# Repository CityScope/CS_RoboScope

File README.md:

# RoboScope

RoboScop project is an motorize platform and three-dimensional interactive simulation platform for the understanding of urban environments. The platform is made of an array of 3D Pixels that can be configured in varying heights and color to represent different urban conditions. In addition, each pixel

## Circuits

Circuits designs in Eagle

## Code

Source code to run the each one of the different project components, server, client, control and interface.

## Docs

Folder includes designs files, drawings, technical data-sheets, and assembly instructions.

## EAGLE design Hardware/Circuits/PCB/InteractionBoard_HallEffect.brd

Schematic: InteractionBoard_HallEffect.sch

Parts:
C1, C2, C3, C4, C5, C6, C7, C8, C9, C12, C13, C14, C15, C16, C17, C18, C19: 0.1uF; 0603-CAP
J3: F-2X10-DIL-2MM; DIL-2MM-2X10
JP1: JUMPER-SMT_3_1-NC_TRACE_NO-SILK; SMT-JUMPER_3_1-NC_TRACE_NO-SILK
JP6, JP7, JP8, JP9, JP10, JP11: JUMPER-SMT_2_NC_TRACE_NO-SILK; SMT-JUMPER_2_NC_TRACE_NO-SILK
M_01, M_02, M_03, M_04, M_05, M_06, M_07, M_08: CONN_06SMD-1MM; 1X06-1MM
POWER_3.3: LEDFAB1206; LED1206FAB
R9, R10, R11, R12, R13, R14, R16, R17, R18, R19, R20, R21, R23, R24, R25, R26: 10K; 0603-RES
R27, R28: 500; 0603-RES
RN1, RN2, RN3: 4R-NEXB38V; EXB38V
S1: JS207011SCQNR; SW_JS207011SCQNR
S2: MOMENTARY-SWITCH-SPST-2-SMD-5.2MM; TACTILE_SWITCH_SMD_5.2MM
STATUS: LEDFAB1206; LED1206FAB
SW1: 219-10; CTS-219-10
SX1509_2, SX1509_3: SX1509; QFN-28
U1, U3, U4, U5, U6, U7, U8, U9: DRV5032FADBZRDBZ0003A_L; DBZ0003A_L
U2: SX1509; QFN-28

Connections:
0_SX1: M_04.6, SX1509_2.27 (I/O[0])
0_SX2: M_08.6, U2.27 (I/O[0])
0_SX3: SX1509_3.27 (I/O[0])
1_SX1: M_04.5, SX1509_2.28 (I/O[1])
1_SX2: M_08.5, U2.28 (I/O[1])
1_SX3: J3.16, SX1509_3.28 (I/O[1])
2_SX1: M_02.6, SX1509_2.1 (I/O[2])
2_SX2: M_06.6, U2.1 (I/O[2])
2_SX3: SX1509_3.1 (I/O[2])
3.3V: C1.1, C2.1, C3.1, C4.1, C5.1, C6.1, C7.1, C8.1, C9.1, C12.1, C13.1, C14.1, C15.1, C16.1, C17.1, C18.1, C19.1, J3.19, R9.2, R10.2, R11.2, R12.2, R13.2, R14.2, R16.2, R17.2, R18.2, R19.2, R20.2, R21.2, R23.2, R24.2, R25.2, R26.2, R27.2, RN1.5 (2), RN1.6 (2), RN1.7 (2), RN1.8 (2), RN2.7 (2), RN2.8 (2), RN3.5 (2), RN3.6 (2), RN3.7 (2), RN3.8 (2), S2.1, S2.2, SX1509_2.4 (VCC1), SX1509_2.12 (VDDM), SX1509_2.18 (VCC2), SX1509_3.4 (VCC1), SX1509_3.12 (VDDM), SX1509_3.18 (VCC2), U1.1 (VCC), U2.4 (VCC1), U2.12 (VDDM), U2.18 (VCC2), U3.1 (VCC), U4.1 (VCC), U5.1 (VCC), U6.1 (VCC), U7.1 (VCC), U8.1 (VCC), U9.1 (VCC)
3_SX1: M_02.5, SX1509_2.2 (I/O[3])
3_SX2: M_06.5, U2.2 (I/O[3])
3_SX3: J3.12, SX1509_3.2 (I/O[3])
4_SX1: M_02.4, SX1509_2.5 (I/O[4])
4_SX2: M_06.4, U2.5 (I/O[4])
4_SX3: JP1.1, SX1509_3.5 (I/O[4])
5_SX1: M_04.4, SX1509_2.6 (I/O[5])
5_SX2: M_08.4, U2.6 (I/O[5])
5_SX3: R28.2, SX1509_3.6 (I/O[5])
6_SX1: SX1509_2.7 (I/O[6]), U3.2 (OUT)
6_SX2: U2.7 (I/O[6]), U7.2 (OUT)
6_SX3: RN1.1, SW1.20, SX1509_3.7 (I/O[6])
7_SX1: SX1509_2.8 (I/O[7]), U5.2 (OUT)
7_SX2: U2.8 (I/O[7]), U9.2 (OUT)
7_SX3: RN1.2 (1), SW1.19, SX1509_3.8 (I/O[7])
8_SX1: SX1509_2.13 (I/O[8]), U1.2 (OUT)
8_SX2: U2.13 (I/O[8]), U6.2 (OUT)
8_SX3: RN1.3 (1), SW1.18, SX1509_3.13 (I/O[8])
9_SX1: SX1509_2.14 (I/O[9]), U4.2 (OUT)
9_SX2: U2.14 (I/O[9]), U8.2 (OUT)
9_SX3: RN1.4 (1), SW1.17, SX1509_3.14 (I/O[9])
10_SX1: M_01.6, SX1509_2.15 (I/O[10])
10_SX2: M_05.6, U2.15 (I/O[10])
10_SX3: RN3.1, SW1.16, SX1509_3.15 (I/O[10])
11_SX1: M_01.5, SX1509_2.16 (I/O[11])
11_SX2: M_05.5, U2.16 (I/O[11])
11_SX3: RN3.2 (1), SW1.15, SX1509_3.16 (I/O[11])
12_SX1: M_01.4, SX1509_2.19 (I/O[12])
12_SX2: M_05.4, U2.19 (I/O[12])
12_SX3: RN3.3 (1), SW1.14, SX1509_3.19 (I/O[12])
13_SX1: M_03.6, SX1509_2.20 (I/O[13])
13_SX2: M_07.6, U2.20 (I/O[13])
13_SX3: RN3.4 (1), SW1.13, SX1509_3.20 (I/O[13])
14_SX1: M_03.5, SX1509_2.21 (I/O[14])
14_SX2: M_07.5, U2.21 (I/O[14])
14_SX3: RN2.1, SW1.12, SX1509_3.21 (I/O[14])
15_SX1: M_03.4, SX1509_2.22 (I/O[15])
15_SX2: M_07.4, U2.22 (I/O[15])
15_SX3: RN2.2 (1), SW1.11, SX1509_3.22 (I/O[15])
!RESET_SX1: R9.1, SX1509_2.23 (!RESET)
!RESET_SX2: R16.1, U2.23 (!RESET)
!RESET_SX3: R14.1, SX1509_3.23 (!RESET)
ADDR0_SX1: JP8.1, SX1509_2.26 (ADDR0)
ADDR0_SX2: JP7.1, U2.26 (ADDR0)
ADDR0_SX3: JP11.1, SX1509_3.26 (ADDR0)
ADDR1_SX1: JP9.1, SX1509_2.10 (ADDR1)
ADDR1_SX2: JP6.1, U2.10 (ADDR1)
ADDR1_SX3: JP10.1, SX1509_3.10 (ADDR1)
GND_MCU: C1.2, C2.2, C3.2, C4.2, C5.2, C6.2, C7.2, C8.2, C9.2, C12.2, C13.2, C14.2, C15.2, C16.2, C17.2, C18.2, C19.2, J3.18, J3.20, JP7.2, JP9.2, M_01.1, M_02.1, M_03.1, M_04.1, M_05.1, M_06.1, M_07.1, M_08.1, POWER_3.3.2 (C), RN2.3 (1), STATUS.2 (C), SW1.1, SW1.2, SW1.3, SW1.4, SW1.5, SW1.6, SW1.7, SW1.8, SW1.9, SW1.10, SX1509_2.3 (GND), SX1509_2.17 (GND), SX1509_2.29 (GND), SX1509_3.3 (GND), SX1509_3.17 (GND), SX1509_3.29 (GND), U1.3 (GND), U2.3 (GND), U2.17 (GND), U2.29 (GND), U3.3 (GND), U4.3 (GND), U5.3 (GND), U6.3 (GND), U7.3 (GND), U8.3 (GND), U9.3 (GND)
INT_01: J3.6, R12.1, SX1509_2.9 (!INT)
INT_02: J3.8, R19.1, U2.9 (!INT)
INT_03: J3.14, R24.1, SX1509_3.9 (!INT)
unnamed: JP6.2, R21.1
unnamed: JP8.2, R13.1
unnamed: R28.1, STATUS.1 (A)
unnamed: JP10.2, R25.1
unnamed: JP11.2, R26.1
unnamed: POWER_3.3.1 (A), R27.1
NEOPIXEL_01: J3.1, M_01.3
NEOPIXEL_02: J3.3, M_02.3
NEOPIXEL_03: J3.5, M_03.3
NEOPIXEL_04: J3.7, M_04.3
NEOPIXEL_05: J3.9, M_05.3
NEOPIXEL_06: J3.11, M_06.3
NEOPIXEL_07: J3.13, M_07.3
NEOPIXEL_08: J3.15, M_08.3
OSCIO_SX1: SX1509_2.11 (OSCIO)
OSCIO_SX2: U2.11 (OSCIO)
OSCIO_SX3: SX1509_3.11 (OSCIO)
RESET: J3.10, JP1.2, JP1.3, RN2.6 (2), S2.3, S2.4
SCL_00: J3.4, R11.1, R18.1, R23.1, SX1509_2.25 (SCL), SX1509_3.25 (SCL), U2.25 (SCL)
SDA_00: J3.2, R10.1, R17.1, R20.1, SX1509_2.24 (SDA), SX1509_3.24 (SDA), U2.24 (SDA)
VCC_5V: M_01.2, M_02.2, M_03.2, M_04.2, M_05.2, M_06.2, M_07.2, M_08.2, S1.4, S1.8
VCC_5V_IN: J3.17, S1.3, S1.7

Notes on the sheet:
INPUTS
Input power line for the BRD
I2C MUX
SWITCH
CONNECTORS
INFO
The VCC1/2 jumpers (SJ2, SJ3) set those pins to 3.3V.
I2C Address Select
VDD Range: 1.425-3.6V
Allowable VCC1/2 Range: 1.2-3.6V
IC2 MUX 01
IC2 MUX 02
IC2 MUX 03

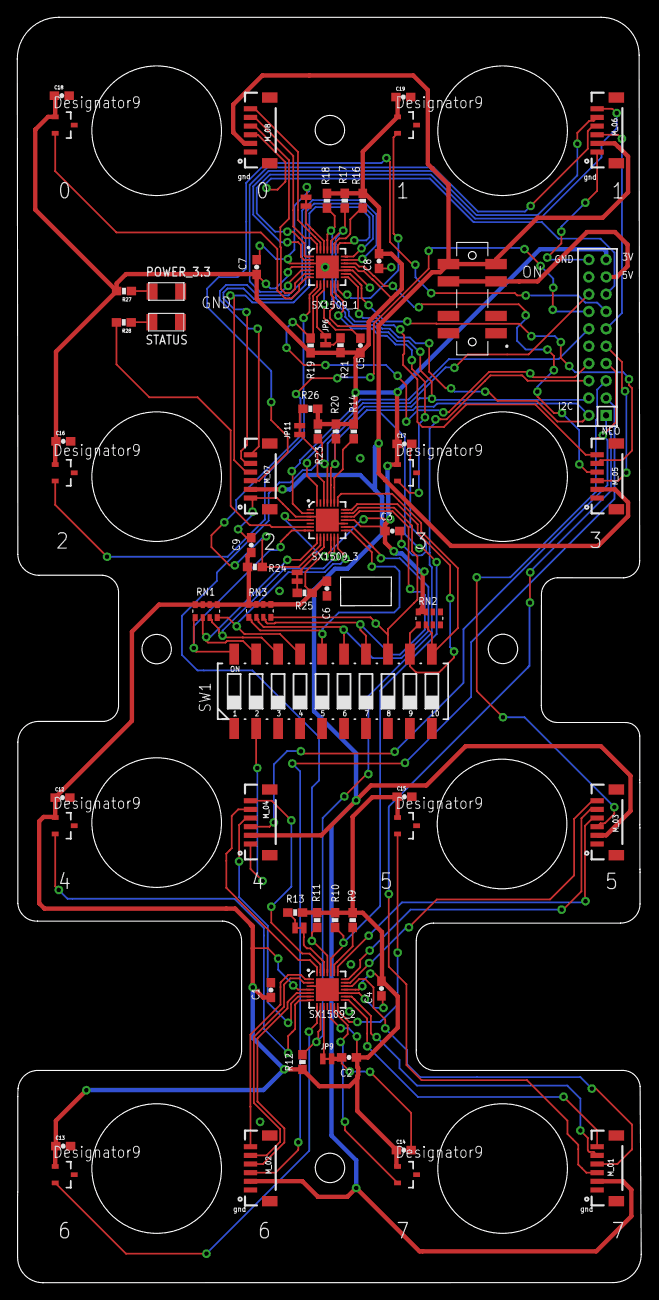
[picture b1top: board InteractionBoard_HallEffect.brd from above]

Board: 2 copper layers, 72.1 x 146.3 mm, 68 parts (0 on the bottom side), 77 nets.

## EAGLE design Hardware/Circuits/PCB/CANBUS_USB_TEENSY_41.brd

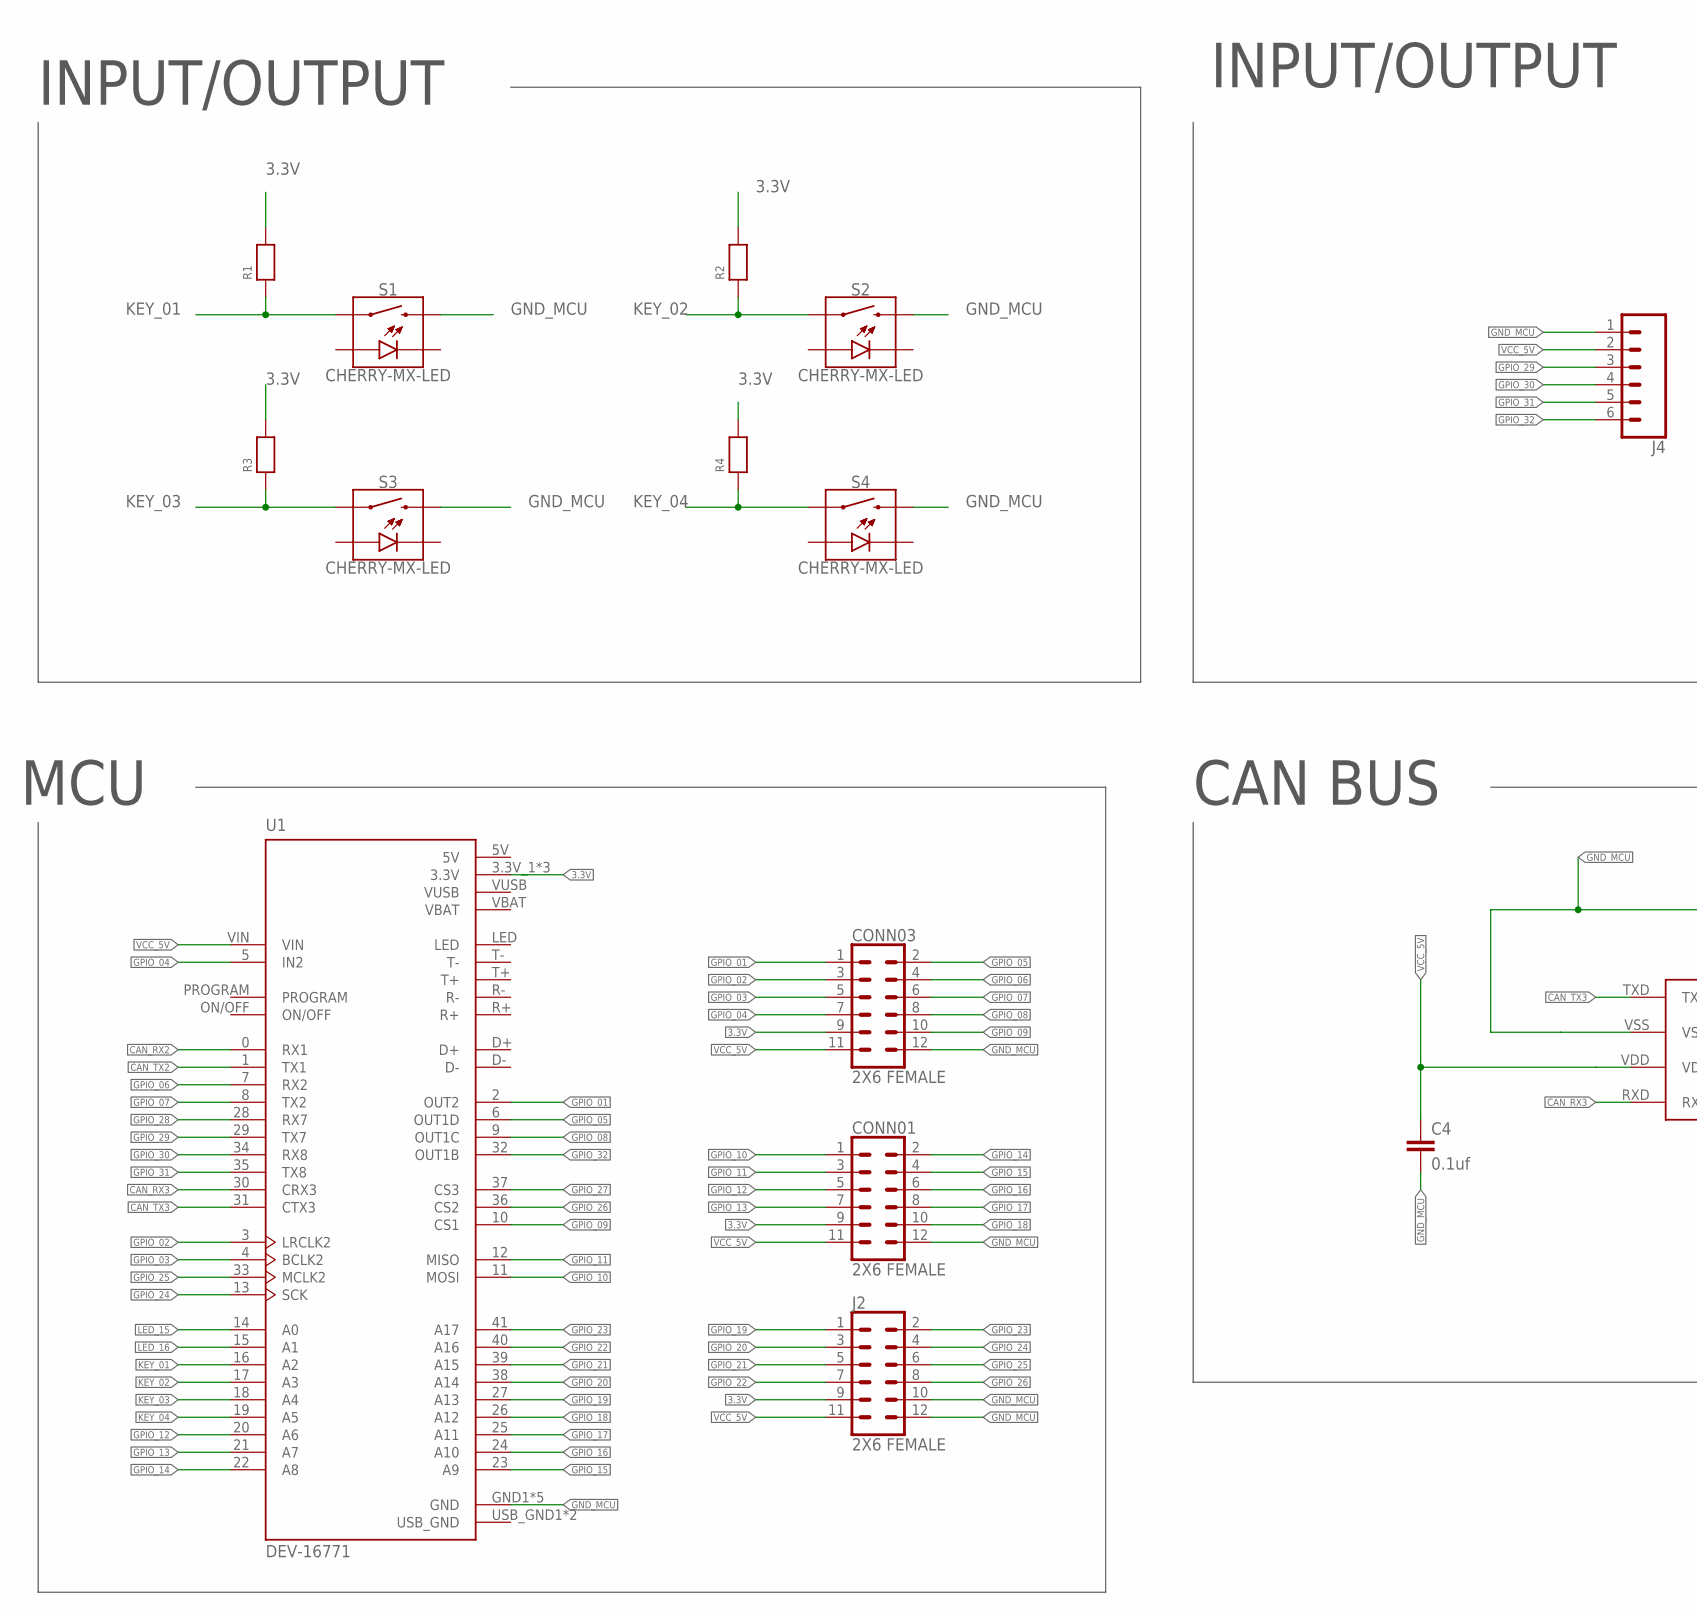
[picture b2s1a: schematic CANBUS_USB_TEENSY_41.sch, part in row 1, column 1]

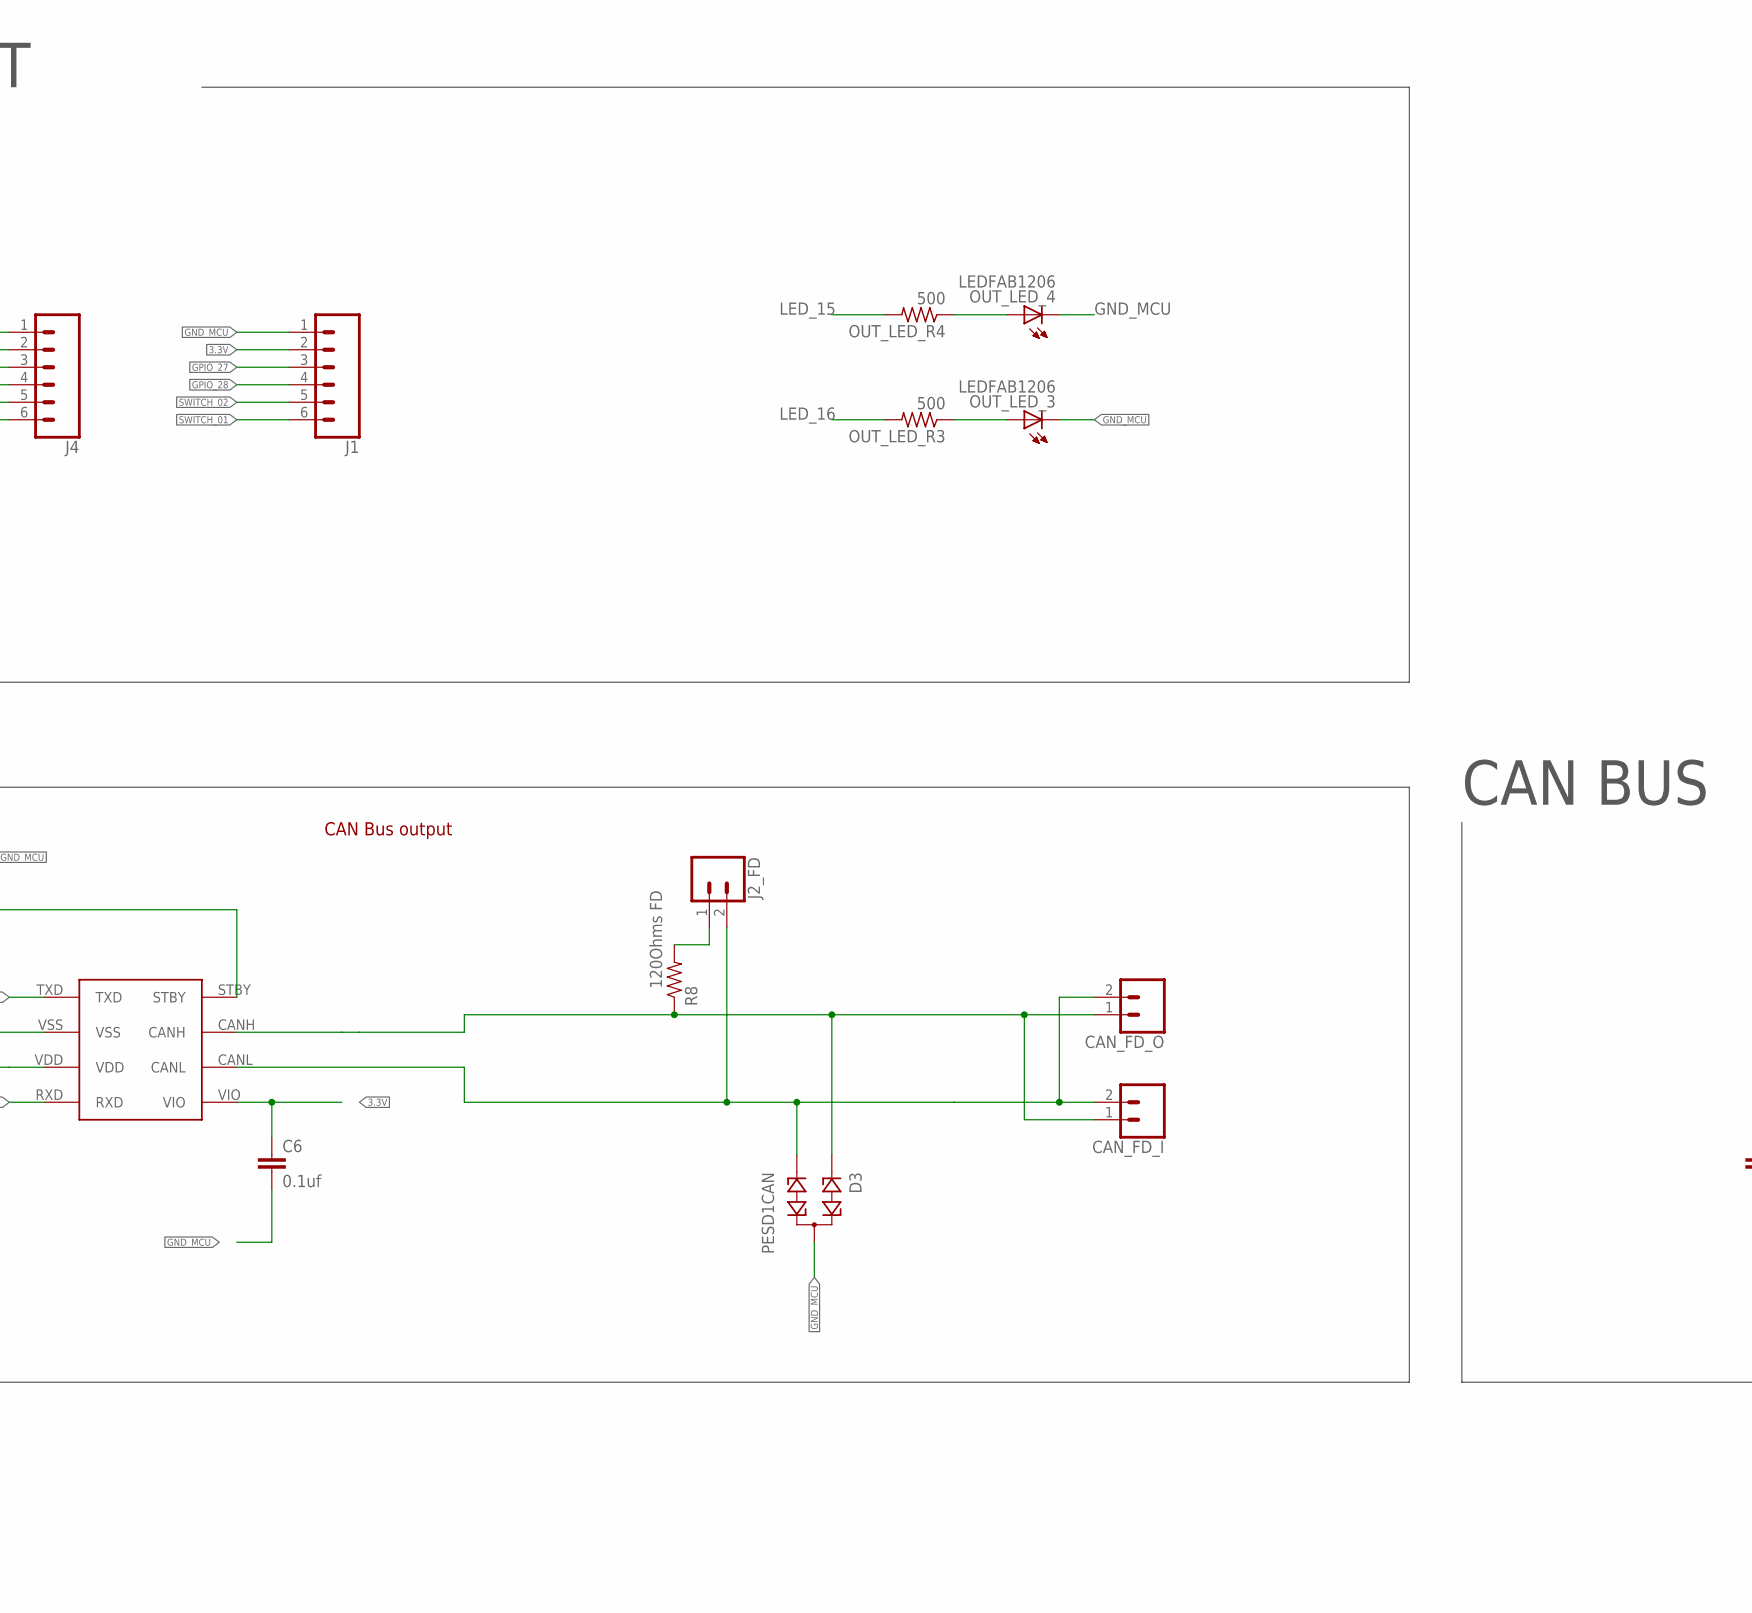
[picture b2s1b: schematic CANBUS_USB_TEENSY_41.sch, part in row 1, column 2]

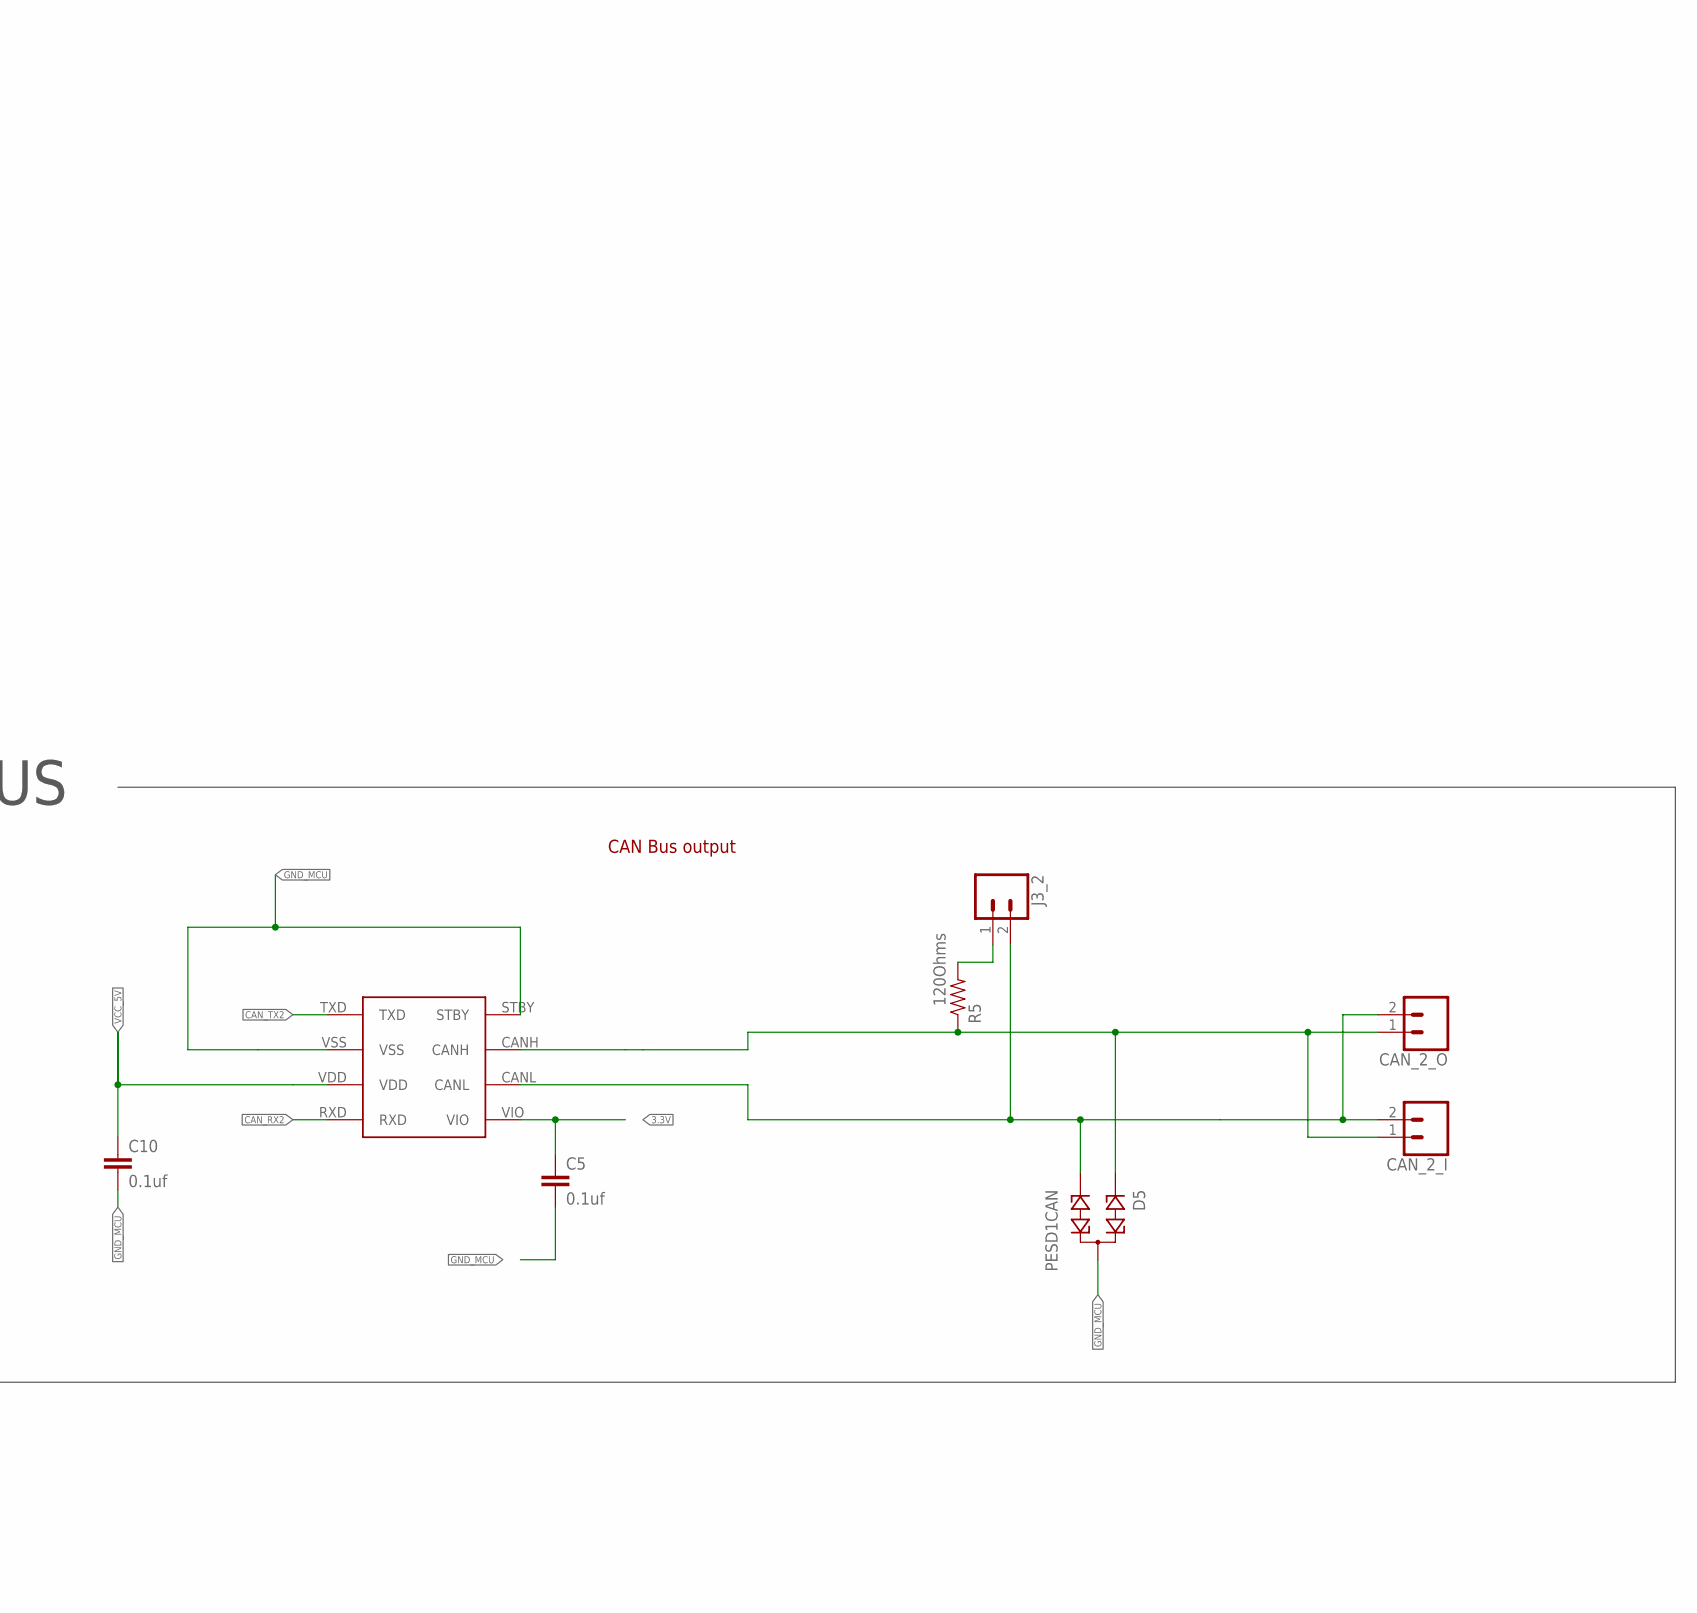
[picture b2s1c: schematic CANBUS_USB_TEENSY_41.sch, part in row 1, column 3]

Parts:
C4, C5, C6, C10: 0.1uf; 0603-CAP
CAN_2_I, CAN_2_O: CONN_02-JST-2MM-SMT; JST-2-SMD
CAN_FD_I: CONN_02-JST-2MM-SMT; JST-2-SMD
CAN_FD_O: CONN_02-JST-2MM-SMT; JST-2-SMD
CONN01, CONN03: 2X6 FEMALE; 2X6
D3, D5: PESD1CAN; SOT23
J1, J4: CONN_06SMD-1MM; 1X06-1MM
J2: 2X6 FEMALE; 2X6
J2_FD, J3_2: CONN_02; 1X02
MCP2562, MCP2562FD: MCP2562
OUT_LED_3, OUT_LED_4: LEDFAB1206; LED1206FAB
OUT_LED_R3, OUT_LED_R4: 500; R1206FAB
R1, R2, R3, R4: RESISTOR1206; 1206
R5: 120Ohms; 0603-RES
R8: 120Ohms FD; 0603-RES
S1, S2, S3, S4: CHERRY-MX-LED
U1: DEV-16771; MODULE_DEV-16771

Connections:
3.3V: C5.1, C6.1, CONN01.9, CONN03.9, J1.2, J2.9, MCP2562.VIO, MCP2562FD.VIO, R1.2, R2.2, R3.2, R4.2, U1.3.3V_1 (3.3V), U1.3.3V_2 (3.3V), U1.3.3V_3 (3.3V)
5V: U1.5V
CAN_H: CAN_FD_I.1 (2), CAN_FD_O.1 (2), D3.1, MCP2562FD.CANH, R8.1
CAN_H1: CAN_2_I.1 (2), CAN_2_O.1 (2), D5.1, MCP2562.CANH, R5.1
CAN_L: CAN_FD_I.2 (1), CAN_FD_O.2 (1), D3.2, J2_FD.2, MCP2562FD.CANL
CAN_L1: CAN_2_I.2 (1), CAN_2_O.2 (1), D5.2, J3_2.2, MCP2562.CANL
CAN_RX2: MCP2562.RXD, U1.0 (RX1)
CAN_RX3: MCP2562FD.RXD, U1.30 (CRX3)
CAN_TX2: MCP2562.TXD, U1.1 (TX1)
CAN_TX3: MCP2562FD.TXD, U1.31 (CTX3)
GND_MCU: C4.2, C5.2, C6.2, C10.2, CONN01.12, CONN03.12, D3.3, D5.3, J1.1, J2.10, J2.12, J4.1, MCP2562.STBY, MCP2562.VSS, MCP2562FD.STBY, MCP2562FD.VSS, OUT_LED_3.2 (C), OUT_LED_4.2 (C), S1.S2, S2.S2, S3.S2, S4.S2, U1.GND1 (GND), U1.GND2 (GND), U1.GND3 (GND), U1.GND4 (GND), U1.GND5 (GND)
GPIO_01: CONN03.1, U1.2 (OUT2)
GPIO_02: CONN03.3, U1.3 (LRCLK2)
GPIO_03: CONN03.5, U1.4 (BCLK2)
GPIO_04: CONN03.7, U1.5 (IN2)
GPIO_05: CONN03.2, U1.6 (OUT1D)
GPIO_06: CONN03.4, U1.7 (RX2)
GPIO_07: CONN03.6, U1.8 (TX2)
GPIO_08: CONN03.8, U1.9 (OUT1C)
GPIO_09: CONN03.10, U1.10 (CS1)
GPIO_10: CONN01.1, U1.11 (MOSI)
GPIO_11: CONN01.3, U1.12 (MISO)
GPIO_12: CONN01.5, U1.20 (A6)
GPIO_13: CONN01.7, U1.21 (A7)
GPIO_14: CONN01.2, U1.22 (A8)
GPIO_15: CONN01.4, U1.23 (A9)
GPIO_16: CONN01.6, U1.24 (A10)
GPIO_17: CONN01.8, U1.25 (A11)
GPIO_18: CONN01.10, U1.26 (A12)
GPIO_19: J2.1, U1.27 (A13)
GPIO_20: J2.3, U1.38 (A14)
GPIO_21: J2.5, U1.39 (A15)
GPIO_22: J2.7, U1.40 (A16)
GPIO_23: J2.2, U1.41 (A17)
GPIO_24: J2.4, U1.13 (SCK)
GPIO_25: J2.6, U1.33 (MCLK2)
GPIO_26: J2.8, U1.36 (CS2)
GPIO_27: J1.3, U1.37 (CS3)
GPIO_28: J1.4, U1.28 (RX7)
GPIO_29: J4.3, U1.29 (TX7)
GPIO_30: J4.4, U1.34 (RX8)
GPIO_31: J4.5, U1.35 (TX8)
GPIO_32: J4.6, U1.32 (OUT1B)
KEY_01: R1.1, S1.S1, U1.16 (A2)
KEY_02: R2.1, S2.S1, U1.17 (A3)
KEY_03: R3.1, S3.S1, U1.18 (A4)
KEY_04: R4.1, S4.S1, U1.19 (A5)
LED_15: OUT_LED_R4.2, U1.14 (A0)
LED_16: OUT_LED_R3.2, U1.15 (A1)
unnamed: J2_FD.1, R8.2
unnamed: J3_2.1, R5.2
unnamed: OUT_LED_3.1 (A), OUT_LED_R3.1
unnamed: OUT_LED_4.1 (A), OUT_LED_R4.1
SWITCH_01: J1.6
SWITCH_02: J1.5
USB_GND: U1.USB_GND1 (USB_GND), U1.USB_GND2 (USB_GND)
VCC_5V: C4.1, C10.1, CONN01.11, CONN03.11, J2.11, J4.2, MCP2562.VDD, MCP2562FD.VDD, U1.VIN

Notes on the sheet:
MCU
INPUT/OUTPUT
CAN BUS
CAN Bus output

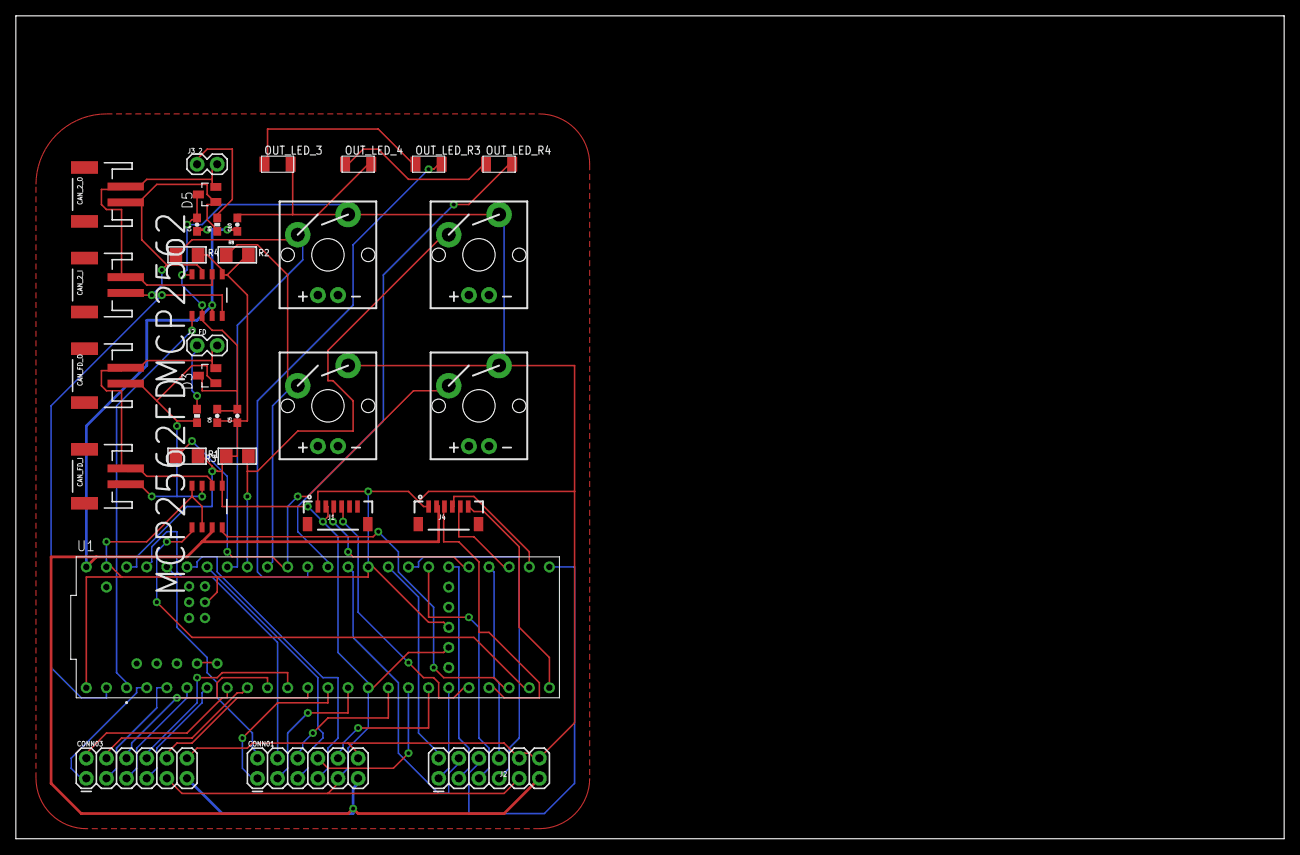
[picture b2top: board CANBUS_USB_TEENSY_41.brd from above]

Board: 2 copper layers, 160.0 x 103.8 mm, 34 parts (0 on the bottom side), 54 nets.

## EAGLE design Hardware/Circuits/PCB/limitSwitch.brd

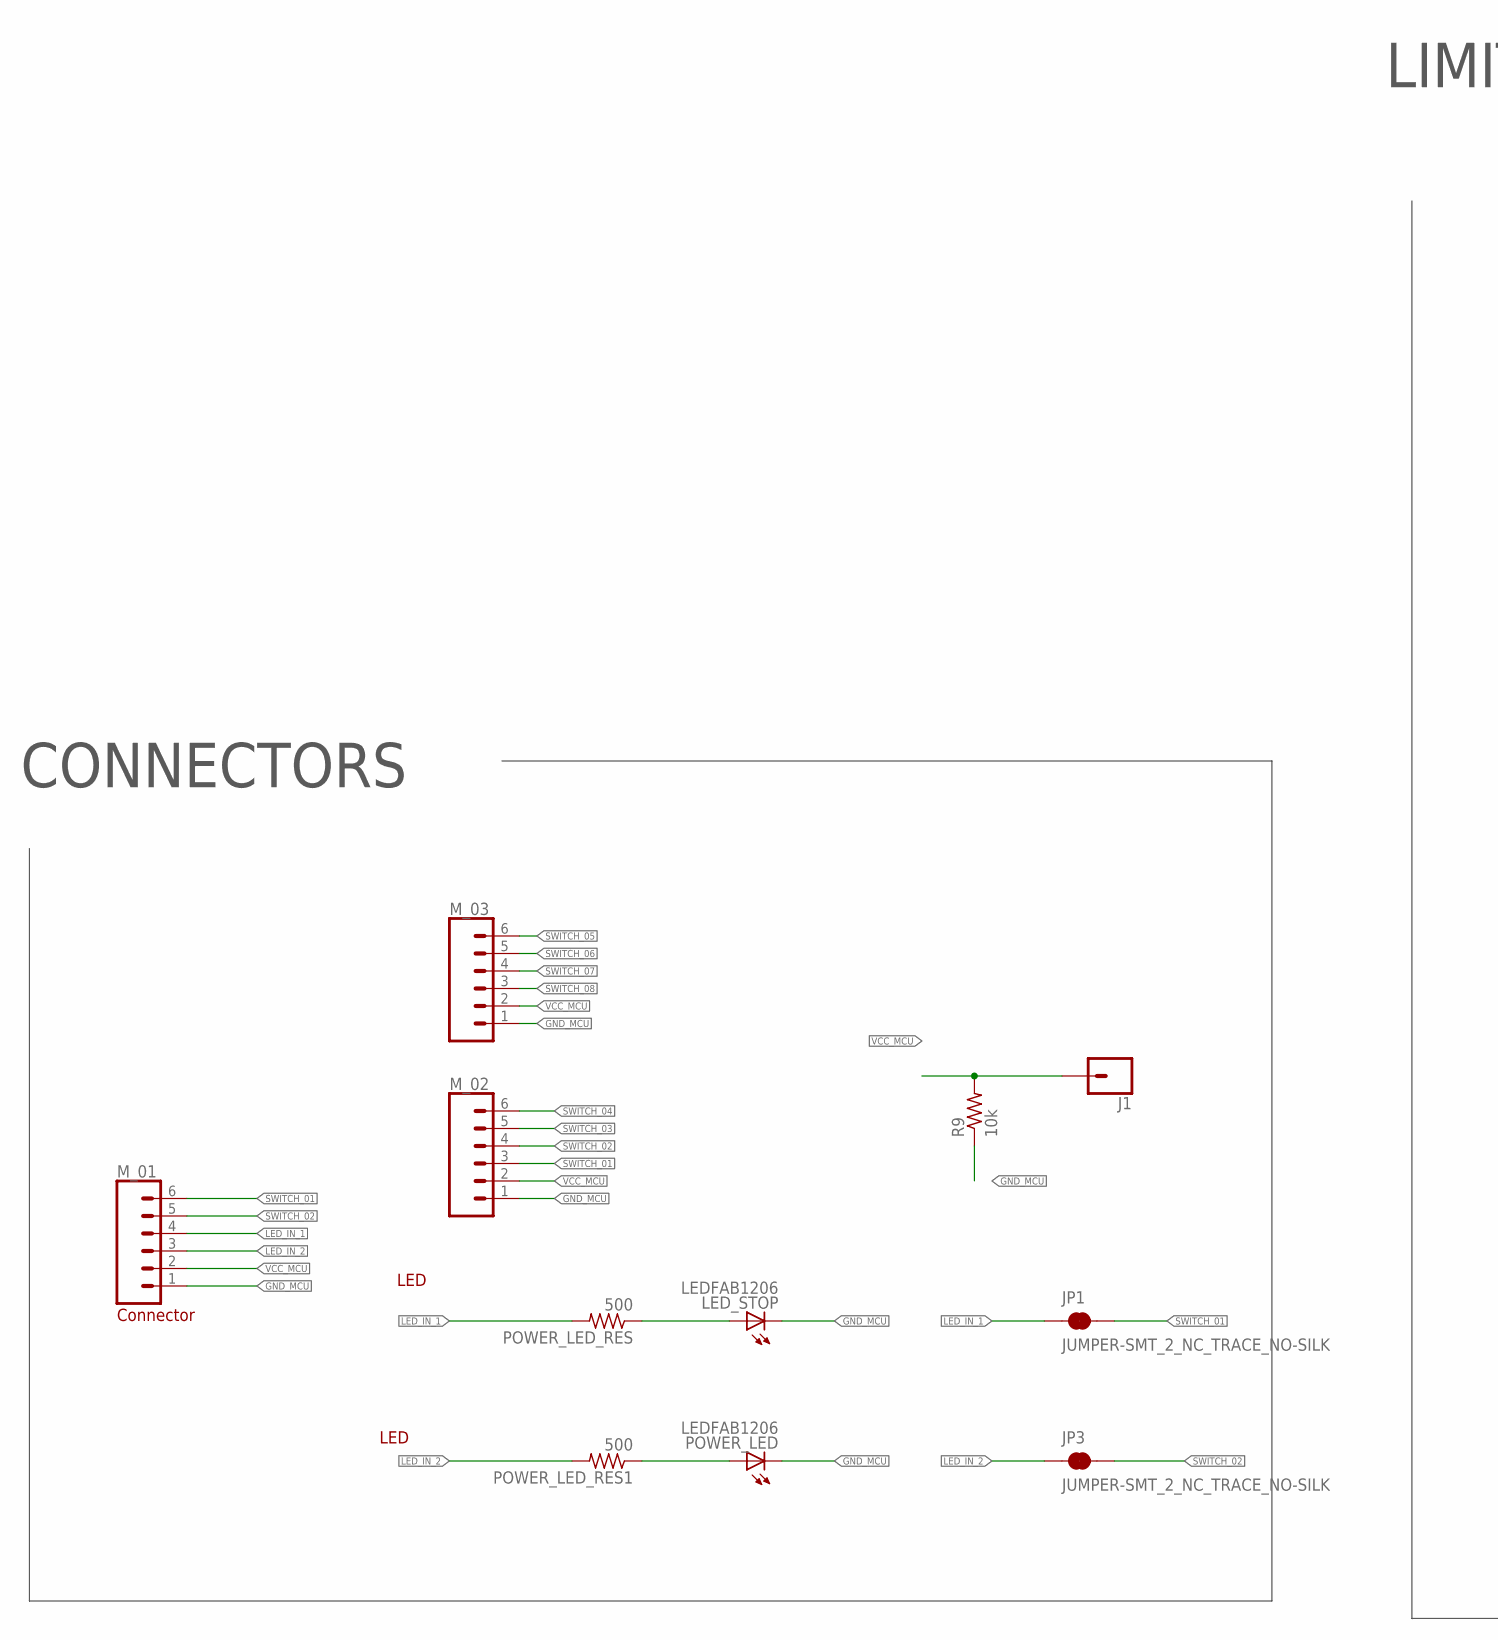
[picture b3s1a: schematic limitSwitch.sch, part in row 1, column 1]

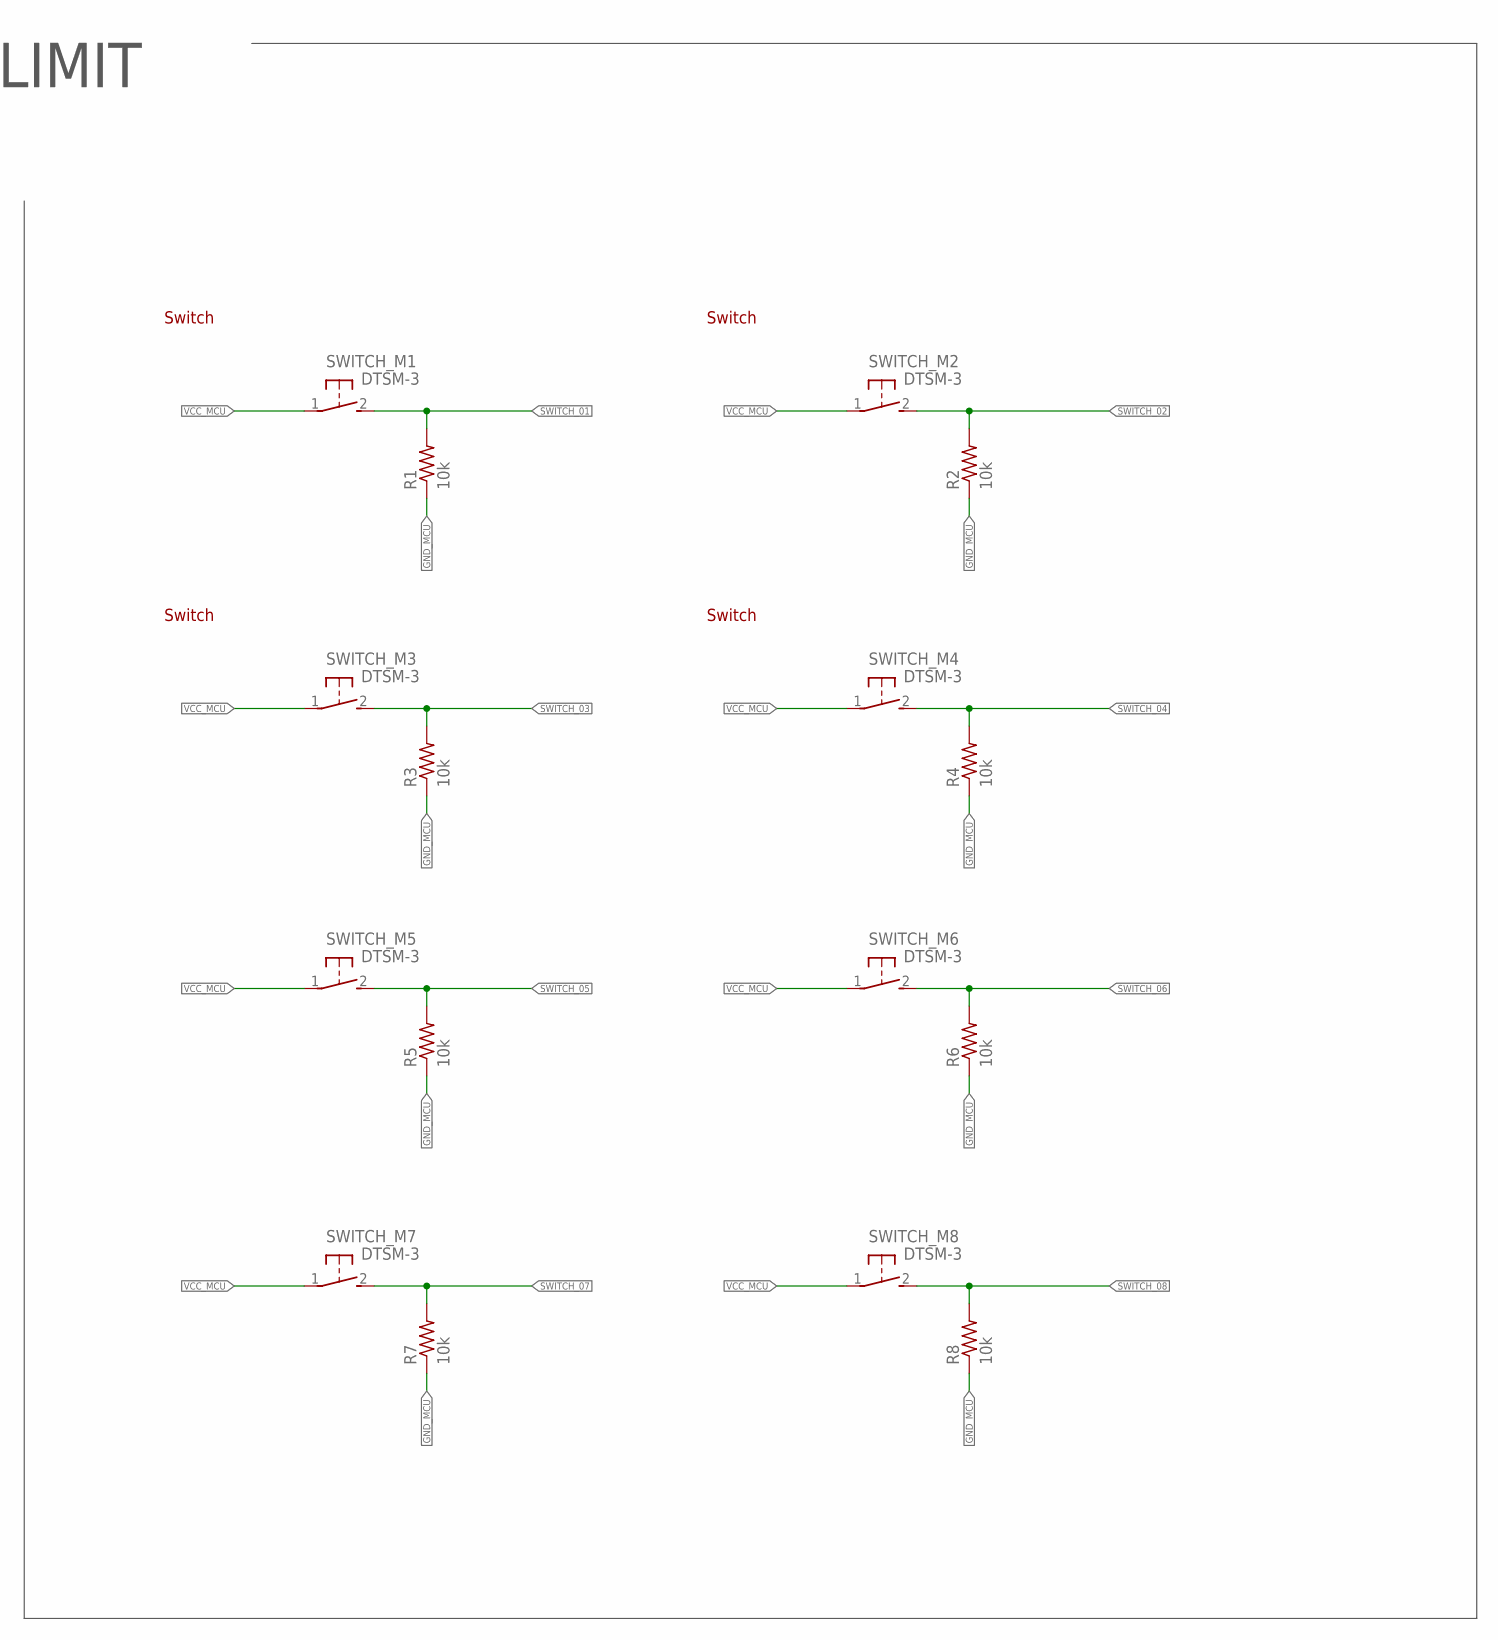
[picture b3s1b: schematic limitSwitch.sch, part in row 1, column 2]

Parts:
J1: CONN_01; 1X01
JP1, JP3: JUMPER-SMT_2_NC_TRACE_NO-SILK; SMT-JUMPER_2_NC_TRACE_NO-SILK
LED_STOP: LEDFAB1206; LED1206FAB
M_01, M_02, M_03: CONN_06SMD-1MM; 1X06-1MM
POWER_LED: LEDFAB1206; LED1206FAB
POWER_LED_RES, POWER_LED_RES1: 500; M0805
R1, R2, R3, R4, R5, R6, R7, R8, R9: 10k; M0805
SWITCH_M1, SWITCH_M2, SWITCH_M3, SWITCH_M4, SWITCH_M5, SWITCH_M6, SWITCH_M7, SWITCH_M8: DTSM-3

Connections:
GND_MCU: LED_STOP.2 (C), M_01.1, M_02.1, M_03.1, POWER_LED.2 (C), R1.1, R2.1, R3.1, R4.1, R5.1, R6.1, R7.1, R8.1, R9.1
LED_IN_1: JP1.1, M_01.4, POWER_LED_RES.2
LED_IN_2: JP3.1, M_01.3, POWER_LED_RES1.2
unnamed: POWER_LED.1 (A), POWER_LED_RES1.1
unnamed: LED_STOP.1 (A), POWER_LED_RES.1
SWITCH_01: JP1.2, M_01.6, M_02.3, R1.2, SWITCH_M1.2
SWITCH_02: JP3.2, M_01.5, M_02.4, R2.2, SWITCH_M2.2
SWITCH_03: M_02.5, R3.2, SWITCH_M3.2
SWITCH_04: M_02.6, R4.2, SWITCH_M4.2
SWITCH_05: M_03.6, R5.2, SWITCH_M5.2
SWITCH_06: M_03.5, R6.2, SWITCH_M6.2
SWITCH_07: M_03.4, R7.2, SWITCH_M7.2
SWITCH_08: M_03.3, R8.2, SWITCH_M8.2
VCC_MCU: J1.1, M_01.2, M_02.2, M_03.2, R9.2, SWITCH_M1.1, SWITCH_M2.1, SWITCH_M3.1, SWITCH_M4.1, SWITCH_M5.1, SWITCH_M6.1, SWITCH_M7.1, SWITCH_M8.1

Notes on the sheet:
CONNECTORS
Connector
LED
Switch
LIMIT

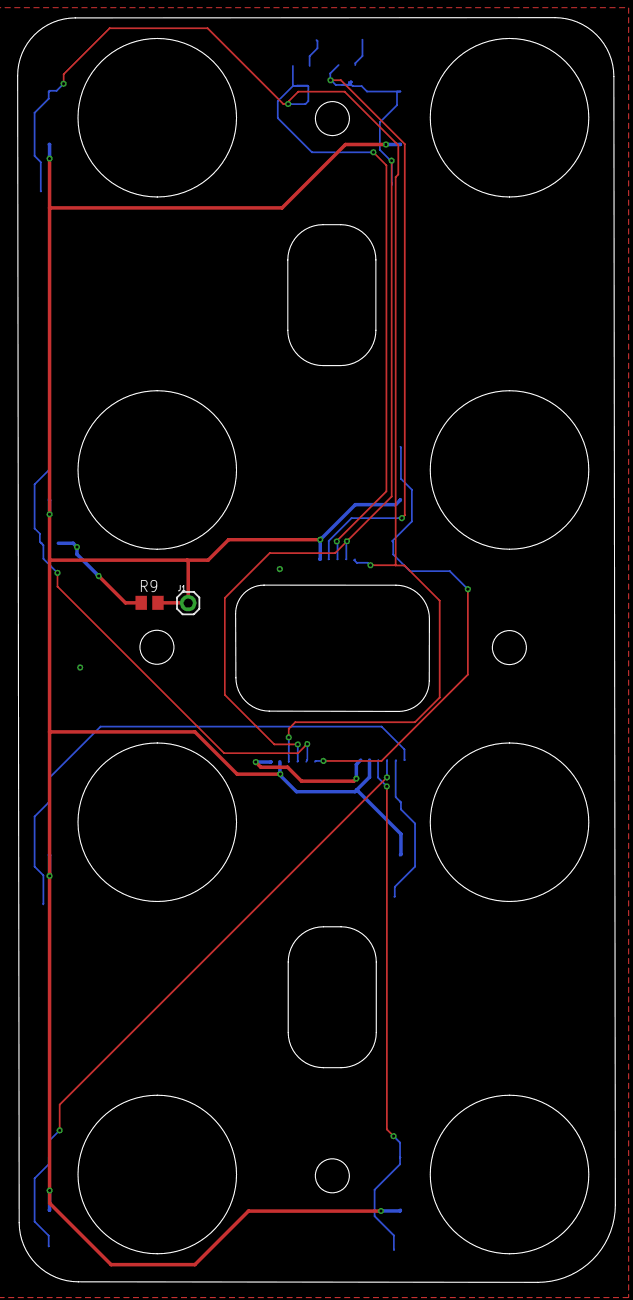
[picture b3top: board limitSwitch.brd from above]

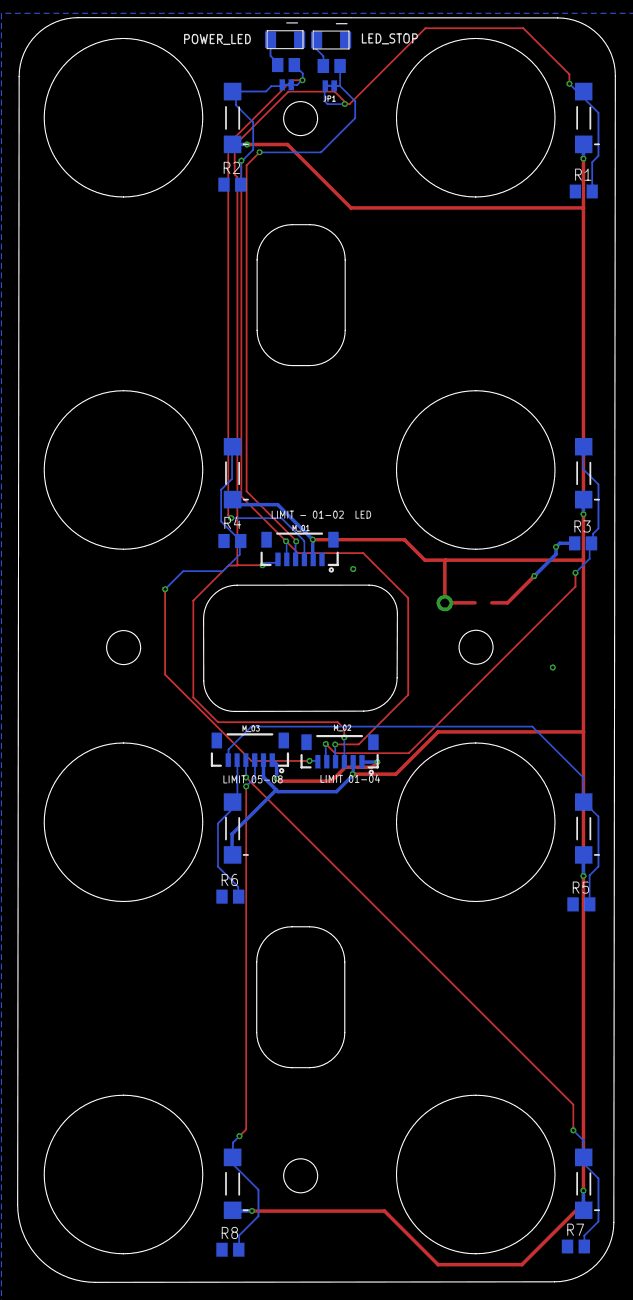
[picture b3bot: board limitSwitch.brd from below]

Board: 2 copper layers, 67.9 x 143.6 mm, 27 parts (25 on the bottom side), 14 nets.

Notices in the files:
parts and their libraries:
SparkFun-Capacitors: Licensing: Creative Commons ShareAlike 4.0 International - https://creativecommons.org/licenses/by-sa/4.0
microbuilder: This work is placed in the public domain, and may be freely used for commercial and non-commercial work with the following conditions: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
